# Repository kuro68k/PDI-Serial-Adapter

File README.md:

# PDI Serial Adapter
 Add logic level RS232 to the PDI/UPDI header, with an FTDI breakout

A simple 2 layer board with 3x (U)PDI headers, and an FTDI cable header. A debug serial port is really handy, and STM debuggers have one built in.

J1 (U)PDI cable to target MCU, 2.54mm pitch<br>
J2 (U)PDI cable to target MCU, 1.27mm pitch<br>
J3 (U)PDI header for debugger/programmer
J4 FTDI cable header for TTL level RS232 and USB power
J5 Easy access to FTDI_VCC (5V or 3.3V depending on the cable)
J6 Connects FTDI_DTR to MCU's reset line via open drain

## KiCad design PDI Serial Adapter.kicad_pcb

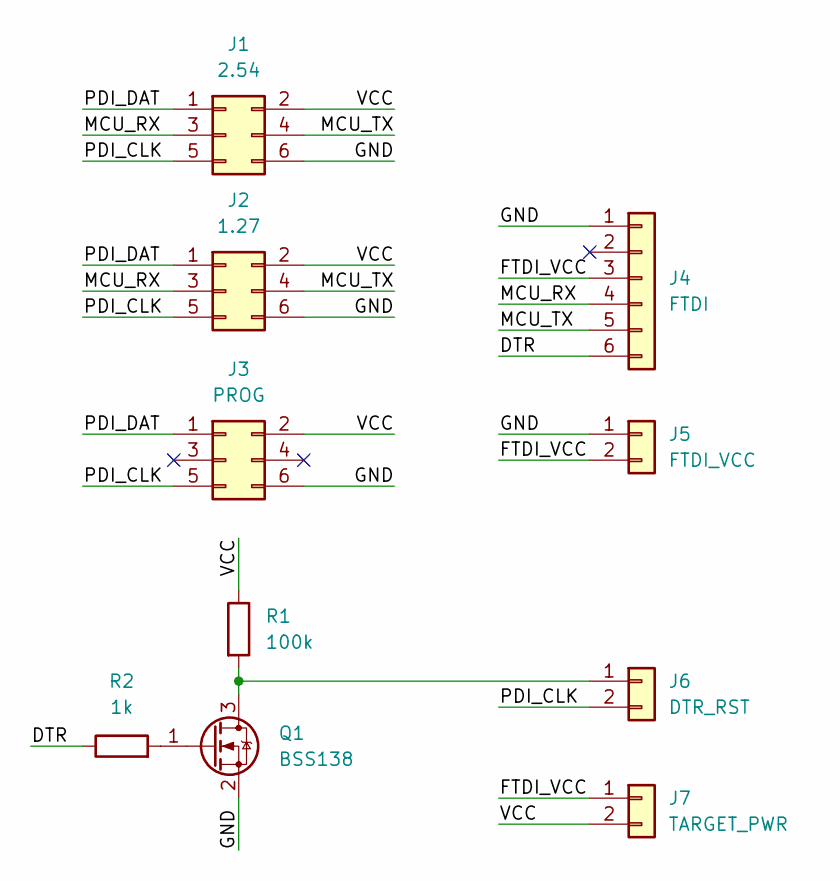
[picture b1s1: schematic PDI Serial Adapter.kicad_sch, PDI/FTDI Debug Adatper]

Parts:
J1: 2.54; PinHeader_2x03_P2.54mm_Vertical
J2: 1.27; PinHeader_2x03_P1.27mm_Vertical
J3: PROG; PinHeader_2x03_P2.54mm_Vertical
J4: FTDI; PinHeader_1x06_P2.54mm_Vertical
J5: FTDI_VCC; PinHeader_1x02_P2.54mm_Vertical
J6: DTR_RST; PinHeader_1x02_P2.54mm_Vertical
J7: TARGET_PWR; PinHeader_1x02_P2.54mm_Vertical
Q1: BSS138; SOT-23
R1: 100k; R_0805_2012Metric_Pad1.20x1.40mm_HandSolder
R2: 1k; R_0805_2012Metric_Pad1.20x1.40mm_HandSolder

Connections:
/DTR: J4.6, R2.1
/FTDI_VCC: J4.3, J5.2, J7.1
/GND: J1.6, J2.6, J3.6, J4.1, J5.1, Q1.2 (S)
/MCU_RX: J1.3, J2.3, J4.4
/MCU_TX: J1.4, J2.4, J4.5
/PDI_CLK: J1.5, J2.5, J3.5, J6.2
/PDI_DAT: J1.1, J2.1, J3.1
/VCC: J1.2, J2.2, J3.2, J7.2, R1.1
unnamed: J6.1, Q1.3 (D), R1.2
unnamed: Q1.1 (G), R2.2

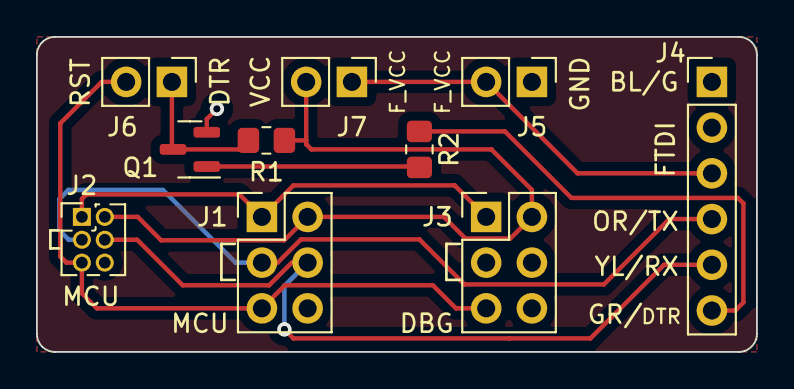
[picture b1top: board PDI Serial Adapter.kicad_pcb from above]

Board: 2 copper layers, 40.0 x 17.5 mm, 10 parts (0 on the bottom side), 10 nets.

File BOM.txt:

Qty	Ref	Value		Footprint
1	J1	2.54		Connector_PinHeader_2.54mm:PinHeader_2x03_P2.54mm_Vertical
1	J2	1.27		Connector_PinHeader_1.27mm:PinHeader_2x03_P1.27mm_Vertical
1	J3	PROG		Connector_PinHeader_2.54mm:PinHeader_2x03_P2.54mm_Vertical
1	J4	FTDI		Connector_PinHeader_2.54mm:PinHeader_1x06_P2.54mm_Vertical
1	J5	FTDI_VCC	Connector_PinHeader_2.54mm:PinHeader_1x02_P2.54mm_Vertical
1	J6	DTR_RST		Connector_PinHeader_2.54mm:PinHeader_1x02_P2.54mm_Vertical
1	J7	TARGET_PWR	Connector_PinHeader_2.54mm:PinHeader_1x02_P2.54mm_Vertical
1	Q1	BSS138		Package_TO_SOT_SMD:SOT-23
1	R1	100k		Resistor_SMD:R_0805_2012Metric_Pad1.20x1.40mm_HandSolder
1	R2	1k			Resistor_SMD:R_0805_2012Metric_Pad1.20x1.40mm_HandSolder

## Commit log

2023-08-19 Removed RX/TX from programmer header
2023-08-19 Open drain for DTR reset
2023-08-19 Update README.md
    Added render
2023-08-20 Added FTDI to silkscreen
2023-09-01 Fabrication settings
2024-06-03 Added BOM

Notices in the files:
PDI Serial Adapter.kicad_pcb:
(C) 2023 kuro68k
Licence: GPLv3
GPLv3
